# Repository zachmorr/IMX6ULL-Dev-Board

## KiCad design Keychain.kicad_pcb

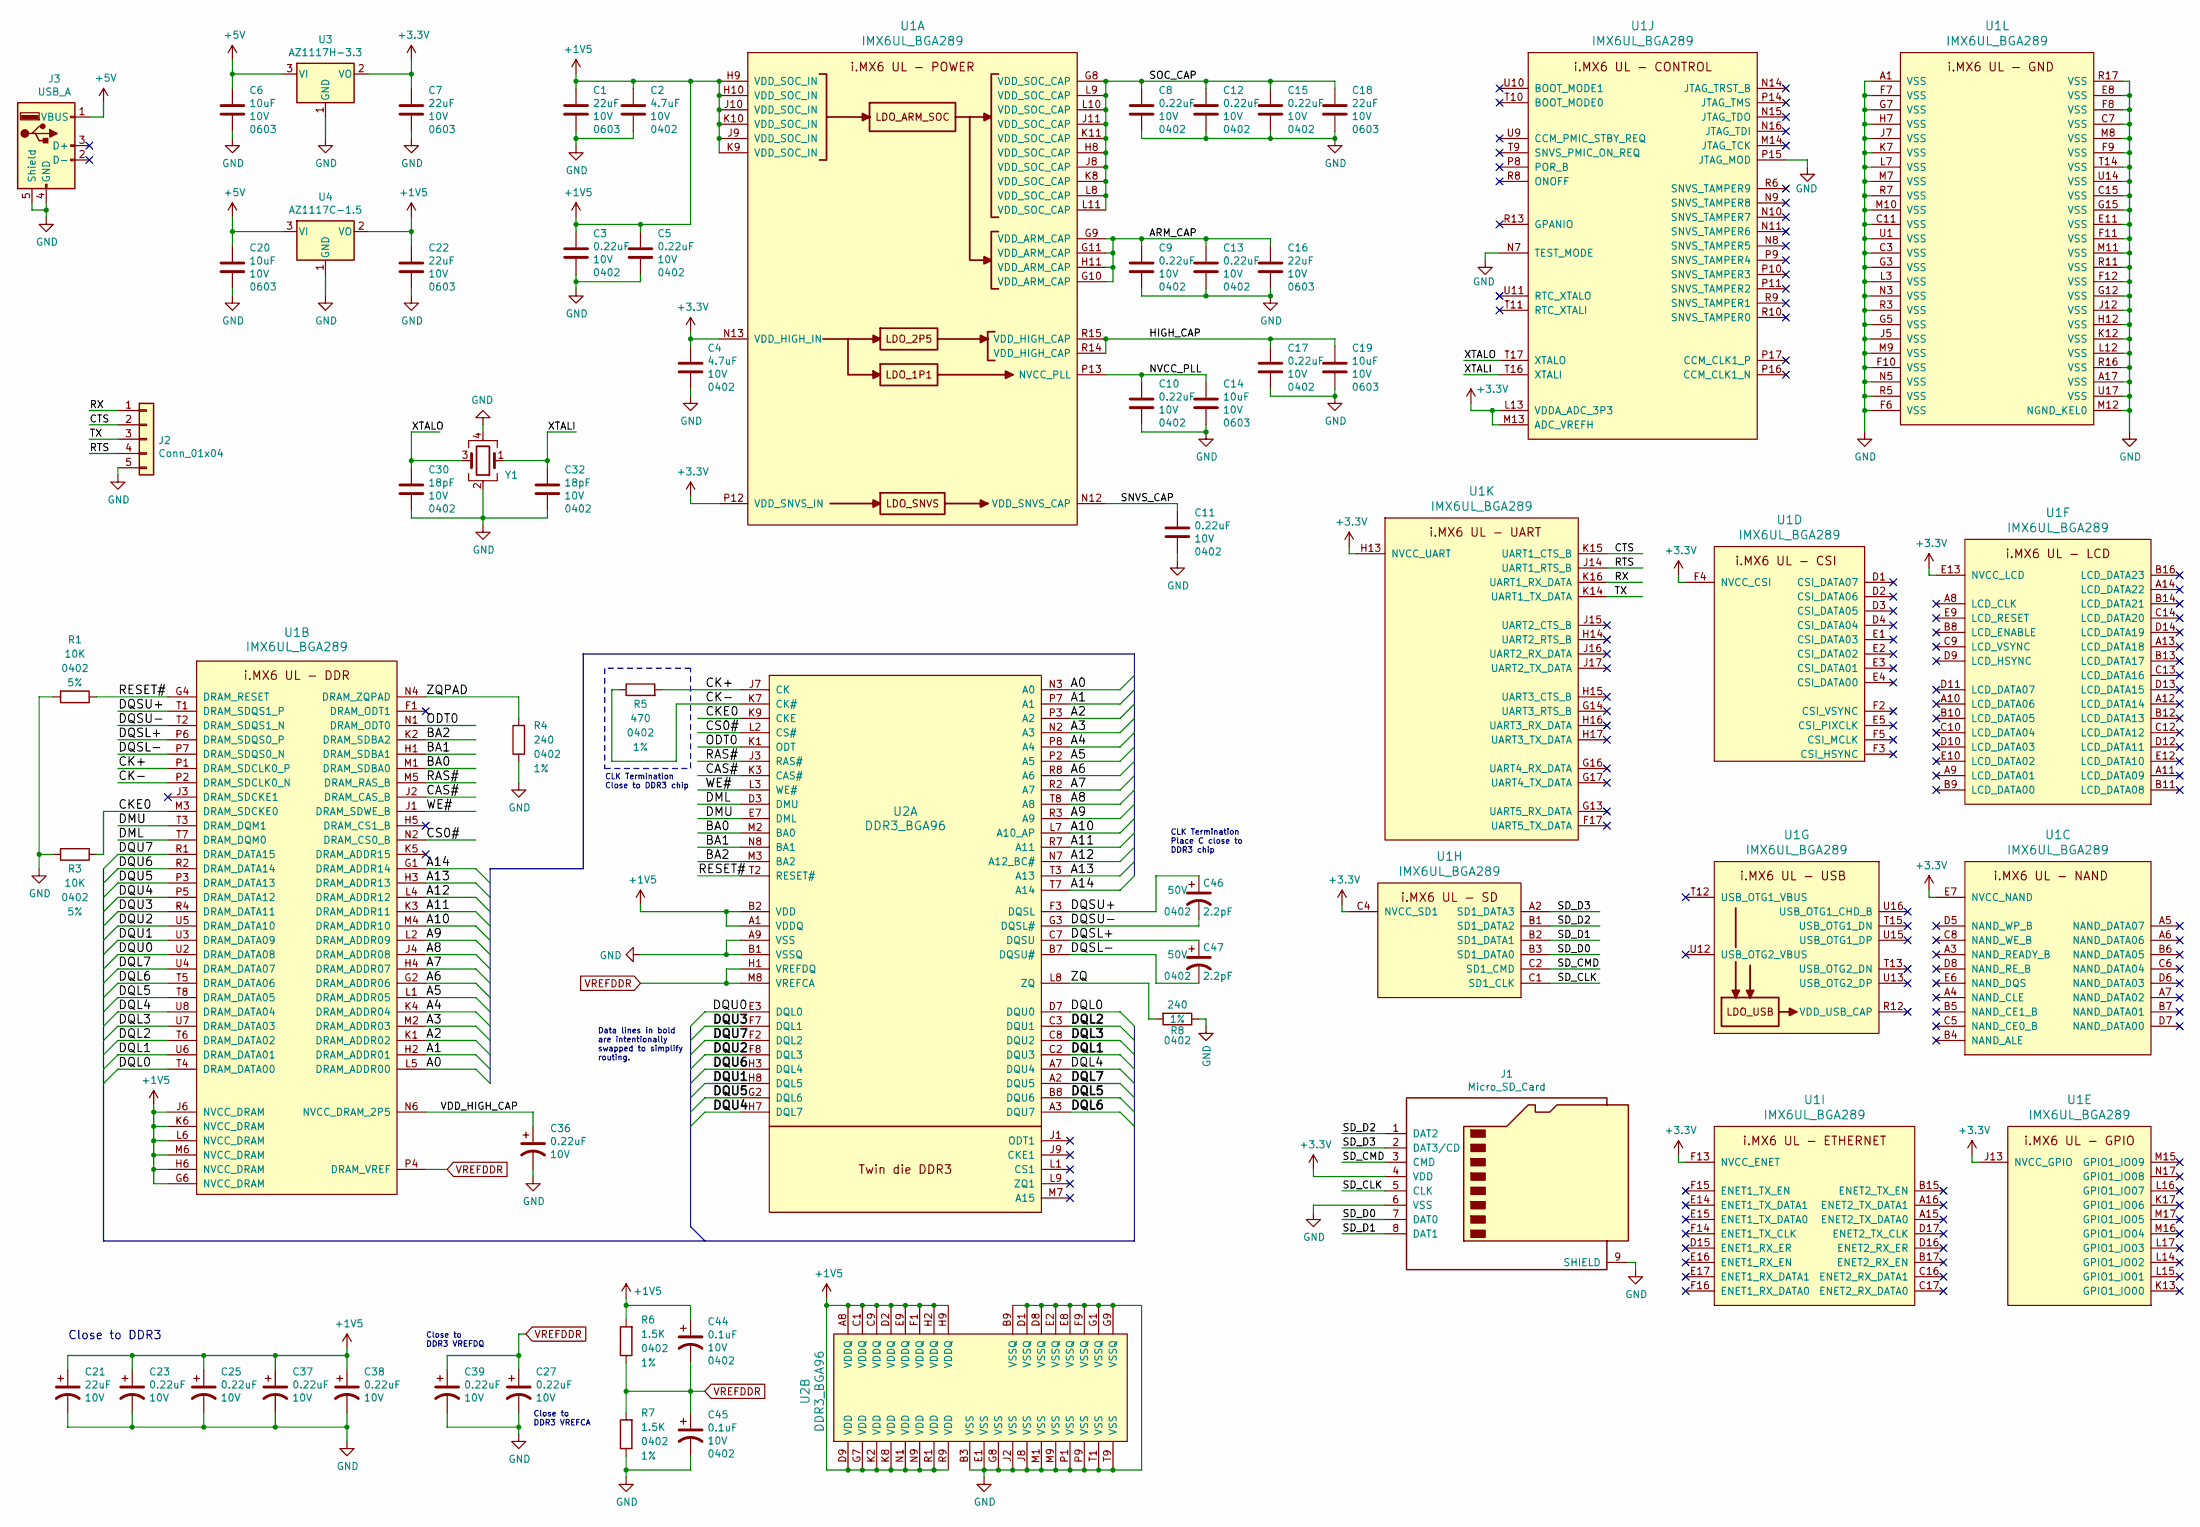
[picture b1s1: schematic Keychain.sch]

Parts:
C1, C7, C16, C18, C21, C22: 22uF; C_0603_1608Metric; Voltage 10V; LCSC C59461
C2, C4: 4.7uF; C_0402_1005Metric; Voltage 10V; LCSC C23733
C3, C5, C8, C9, C10, C11, C12, C13, C15, C17, C23, C25, C27, C36, C37, C38, C39: 0.22uF; C_0402_1005Metric; Voltage 10V; LCSC C16772
C6, C14, C19, C20: 10uF; C_0603_1608Metric; Voltage 10V; LCSC C15525
C30, C32: 18pF; C_0402_1005Metric; Voltage 10V; LCSC C1549
C44, C45: 0.1uF; C_0402_1005Metric; Voltage 10V; LCSC C1525
C46, C47: 2.2pF; C_0402_1005Metric; Voltage 50V; LCSC C1559
J1: Micro_SD_Card; microSD_HC_Molex_104031-0811
J2: Conn_01x04; PinHeader_1x05_P2.54mm_Vertical
J3: USB_A; USB_A_Molex_67643_Horizontal
R1, R3: 10K; R_0402_1005Metric; Tolerance 5%; LCSC C25744
R4, R8: 240; R_0402_1005Metric; Tolerance 1%; LCSC C25094
R5: 470; R_0402_1005Metric; Tolerance 1%; LCSC C25792
R6, R7: 1.5K; R_0402_1005Metric; Tolerance 1%; LCSC C25867
U1: IMX6UL_BGA289; LCSC C394784
U2: DDR3_BGA96; LCSC C36513
U3: AZ1117H-3.3; SOT-223; LCSC C92517
U4: AZ1117C-1.5; SOT-223; LCSC C92108
Y1: Crystal_GND24; Crystal_SMD_3225-4Pin_3.2x2.5mm; LCSC C91744

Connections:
+1V5: C1.1, C2.1, C3.1, C5.1, C21.1, C22.1, C23.1, C25.1, C37.1, C38.1, C44.1, R6.2, U1.G6 (NVCC_DRAM), U1.H6 (NVCC_DRAM), U1.H9 (VDD_SOC_IN), U1.H10 (VDD_SOC_IN), U1.J6 (NVCC_DRAM), U1.J9 (VDD_SOC_IN), U1.J10 (VDD_SOC_IN), U1.K6 (NVCC_DRAM), U1.K9 (VDD_SOC_IN), U1.K10 (VDD_SOC_IN), U1.L6 (NVCC_DRAM), U1.M6 (NVCC_DRAM), U2.A1 (VDDQ), U2.A8 (VDDQ), U2.B2 (VDD), U2.C1 (VDDQ), U2.C9 (VDDQ), U2.D2 (VDDQ), U2.D9 (VDD), U2.E9 (VDDQ), U2.F1 (VDDQ), U2.G7 (VDD), U2.H2 (VDDQ), U2.H9 (VDDQ), U2.K2 (VDD), U2.K8 (VDD), U2.N1 (VDD), U2.N9 (VDD), U2.R1 (VDD), U2.R9 (VDD), U4.2 (VO)
+3V3: C4.1, C7.1, J1.4 (VDD), U1.C4 (NVCC_SD1), U1.E7 (NVCC_NAND), U1.E13 (NVCC_LCD), U1.F4 (NVCC_CSI), U1.F13 (NVCC_ENET), U1.H13 (NVCC_UART), U1.J13 (NVCC_GPIO), U1.L13 (VDDA_ADC_3P3), U1.M13 (ADC_VREFH), U1.N13 (VDD_HIGH_IN), U1.P12 (VDD_SNVS_IN), U3.2 (VO)
+5V: C6.1, C20.1, J3.1 (VBUS), U3.3 (VI), U4.3 (VI)
/A0: U1.L5 (DRAM_ADDR00), U2.N3 (A0)
/A1: U1.H2 (DRAM_ADDR01), U2.P7 (A1)
/A2: U1.K1 (DRAM_ADDR02), U2.P3 (A2)
/A3: U1.M2 (DRAM_ADDR03), U2.N2 (A3)
/A4: U1.K4 (DRAM_ADDR04), U2.P8 (A4)
/A5: U1.L1 (DRAM_ADDR05), U2.P2 (A5)
/A6: U1.G2 (DRAM_ADDR06), U2.R8 (A6)
/A7: U1.H4 (DRAM_ADDR07), U2.R2 (A7)
/A8: U1.J4 (DRAM_ADDR08), U2.T8 (A8)
/A9: U1.L2 (DRAM_ADDR09), U2.R3 (A9)
/A10: U1.M4 (DRAM_ADDR10), U2.L7 (A10_AP)
/A11: U1.K3 (DRAM_ADDR11), U2.R7 (A11)
/A12: U1.L4 (DRAM_ADDR12), U2.N7 (A12_BC#)
/A13: U1.H3 (DRAM_ADDR13), U2.T3 (A13)
/A14: U1.G1 (DRAM_ADDR14), U2.T7 (A14)
/ARM_CAP: C9.1, C13.1, C16.1, U1.G9 (VDD_ARM_CAP), U1.G10 (VDD_ARM_CAP), U1.G11 (VDD_ARM_CAP), U1.H11 (VDD_ARM_CAP)
/BA0: U1.M1 (DRAM_SDBA0), U2.M2 (BA0)
/BA1: U1.H1 (DRAM_SDBA1), U2.N8 (BA1)
/BA2: U1.K2 (DRAM_SDBA2), U2.M3 (BA2)
/CAS#: U1.J2 (DRAM_CAS_B), U2.K3 (CAS#)
/CK+: R5.2, U1.P1 (DRAM_SDCLK0_P), U2.J7 (CK)
/CK-: R5.1, U1.P2 (DRAM_SDCLK0_N), U2.K7 (CK#)
/CKE0: R3.1, U1.M3 (DRAM_SDCKE0), U2.K9 (CKE)
/CS0#: U1.N2 (DRAM_CS0_B), U2.L2 (CS#)
/CTS: J2.2, U1.K15 (UART1_CTS_B)
/DML: U1.T7 (DRAM_DQM0), U2.D3 (DMU)
/DMU: U1.T3 (DRAM_DQM1), U2.E7 (DML)
/DQL0: U1.T4 (DRAM_DATA00), U2.D7 (DQU0)
/DQL1: U1.U6 (DRAM_DATA01), U2.C2 (DQU3)
/DQL2: U1.T6 (DRAM_DATA02), U2.C3 (DQU1)
/DQL3: U1.U7 (DRAM_DATA03), U2.C8 (DQU2)
/DQL4: U1.U8 (DRAM_DATA04), U2.A7 (DQU4)
/DQL5: U1.T8 (DRAM_DATA05), U2.B8 (DQU6)
/DQL6: U1.T5 (DRAM_DATA06), U2.A3 (DQU7)
/DQL7: U1.U4 (DRAM_DATA07), U2.A2 (DQU5)
/DQSL+: C47.1, U1.P6 (DRAM_SDQS0_P), U2.C7 (DQSU)
/DQSL-: C47.2, U1.P7 (DRAM_SDQS0_N), U2.B7 (DQSU#)
/DQSU+: C46.1, U1.T1 (DRAM_SDQS1_P), U2.F3 (DQSL)
/DQSU-: C46.2, U1.T2 (DRAM_SDQS1_N), U2.G3 (DQSL#)
/DQU0: U1.U2 (DRAM_DATA08), U2.E3 (DQL0)
/DQU1: U1.U3 (DRAM_DATA09), U2.H8 (DQL5)
/DQU2: U1.U5 (DRAM_DATA10), U2.F8 (DQL3)
/DQU3: U1.R4 (DRAM_DATA11), U2.F7 (DQL1)
/DQU4: U1.P5 (DRAM_DATA12), U2.H7 (DQL7)
/DQU5: U1.P3 (DRAM_DATA13), U2.G2 (DQL6)
/DQU6: U1.R2 (DRAM_DATA14), U2.H3 (DQL4)
/DQU7: U1.R1 (DRAM_DATA15), U2.F2 (DQL2)
/HIGH_CAP: C17.1, C19.1, U1.R14 (VDD_HIGH_CAP), U1.R15 (VDD_HIGH_CAP)
/NVCC_PLL: C10.1, C14.1, U1.P13 (NVCC_PLL)
/ODT0: U1.N1 (DRAM_ODT0), U2.K1 (ODT)
/RAS#: U1.M5 (DRAM_RAS_B), U2.J3 (RAS#)
/RESET#: R1.1, U1.G4 (DRAM_RESET), U2.T2 (RESET#)
/RTS: J2.4, U1.J14 (UART1_RTS_B)
/RX: J2.1, U1.K16 (UART1_RX_DATA)
/SD_CLK: J1.5 (CLK), U1.C1 (SD1_CLK)
/SD_CMD: J1.3 (CMD), U1.C2 (SD1_CMD)
/SD_D0: J1.7 (DAT0), U1.B3 (SD1_DATA0)
/SD_D1: J1.8 (DAT1), U1.B2 (SD1_DATA1)
/SD_D2: J1.1 (DAT2), U1.B1 (SD1_DATA2)
/SD_D3: J1.2 (DAT3/CD), U1.A2 (SD1_DATA3)
/SNVS_CAP: C11.1, U1.N12 (VDD_SNVS_CAP)
/SOC_CAP: C8.1, C12.1, C15.1, C18.1, U1.G8 (VDD_SOC_CAP), U1.H8 (VDD_SOC_CAP), U1.J8 (VDD_SOC_CAP), U1.J11 (VDD_SOC_CAP), U1.K8 (VDD_SOC_CAP), U1.K11 (VDD_SOC_CAP), U1.L8 (VDD_SOC_CAP), U1.L9 (VDD_SOC_CAP), U1.L10 (VDD_SOC_CAP), U1.L11 (VDD_SOC_CAP)
/TX: J2.3, U1.K14 (UART1_TX_DATA)
/VDD_HIGH_CAP: C36.1, U1.N6 (NVCC_DRAM_2P5)
/WE#: U1.J1 (DRAM_SDWE_B), U2.L3 (WE#)
/XTALI: C32.1, U1.T16 (XTALI), Y1.1
/XTALO: C30.1, U1.T17 (XTALO), Y1.3
/ZQ: R8.2, U2.L8 (ZQ)
/ZQPAD: R4.2, U1.N4 (DRAM_ZQPAD)
GND: C1.2, C2.2, C3.2, C4.2, C5.2, C6.2, C7.2, C8.2, C9.2, C10.2, C11.2, C12.2, C13.2, C14.2, C15.2, C16.2, C17.2, C18.2, C19.2, C20.2, C21.2, C22.2, C23.2, C25.2, C27.2, C30.2, C32.2, C36.2, C37.2, C38.2, C39.2, C45.2, J1.6 (VSS), J1.9 (SHIELD), J2.5, J3.4 (GND), J3.5 (Shield), R1.2, R3.2, R4.1, R7.1, R8.1, U1.A1 (VSS), U1.A17 (VSS), U1.C3 (VSS), U1.C7 (VSS), U1.C11 (VSS), U1.C15 (VSS), U1.E8 (VSS), U1.E11 (VSS), U1.F6 (VSS), U1.F7 (VSS), U1.F8 (VSS), U1.F9 (VSS), U1.F10 (VSS), U1.F11 (VSS), U1.F12 (VSS), U1.G3 (VSS), U1.G5 (VSS), U1.G7 (VSS), U1.G12 (VSS), U1.G15 (VSS), U1.H7 (VSS), U1.H12 (VSS), U1.J5 (VSS), U1.J7 (VSS), U1.J12 (VSS), U1.K7 (VSS), U1.K12 (VSS), U1.L3 (VSS), U1.L7 (VSS), U1.L12 (VSS), U1.M7 (VSS), U1.M8 (VSS), U1.M9 (VSS), U1.M10 (VSS), U1.M11 (VSS), U1.M12 (NGND_KEL0), U1.N3 (VSS), U1.N5 (VSS), U1.N7 (TEST_MODE), U1.P15 (JTAG_MOD), U1.R3 (VSS), U1.R5 (VSS), U1.R7 (VSS), U1.R11 (VSS), U1.R16 (VSS), U1.R17 (VSS), U1.T14 (VSS), U1.U1 (VSS), U1.U14 (VSS), U1.U17 (VSS), U2.A9 (VSS), U2.B1 (VSSQ), U2.B3 (VSS), U2.B9 (VSSQ), U2.D1 (VSSQ), U2.D8 (VSSQ), U2.E1 (VSS), U2.E2 (VSSQ), U2.E8 (VSSQ), U2.F9 (VSSQ), U2.G1 (VSSQ), U2.G8 (VSS), U2.G9 (VSSQ), U2.J2 (VSS), U2.J8 (VSS), U2.M1 (VSS), U2.M9 (VSS), U2.P1 (VSS), U2.P9 (VSS), U2.T1 (VSS), U2.T9 (VSS), U3.1 (GND), U3.4, U4.1 (GND), U4.4, Y1.2, Y1.4
VREFDDR: C27.1, C39.1, C44.2, C45.1, R6.1, R7.2, U1.P4 (DRAM_VREF), U2.H1 (VREFDQ), U2.M8 (VREFCA)

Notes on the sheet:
CLK Termination Place C close to DDR3 chip
Data lines in bold are intentionally swapped to simplify routing.
CLK Termination Close to DDR3 chip
Close to DDR3
Close to DDR3 VREFCA
Close to DDR3 VREFDQ

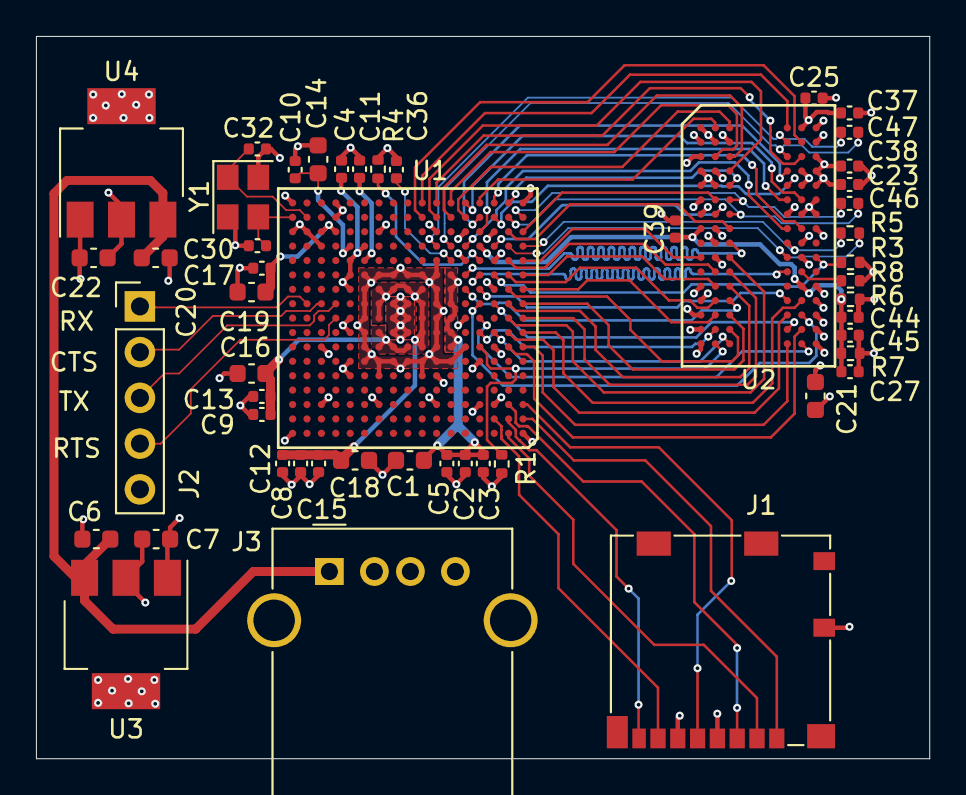
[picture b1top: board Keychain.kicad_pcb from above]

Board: 4 copper layers, 49.6 x 40.1 mm, 50 parts (0 on the bottom side), 74 nets.

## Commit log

2020-11-16 Adding KiCad project
2020-11-20 DDR nets are connected, now needs length tuning
2020-11-24 Completed DDR routing & length matching
2020-11-25 Added some LDO and connectors, still need to finish routing
2020-12-15 Finished first version of board
2020-12-15 Moved some parts to bottom for easier assembly
2021-05-14 New layout!
2021-06-18 New layout
